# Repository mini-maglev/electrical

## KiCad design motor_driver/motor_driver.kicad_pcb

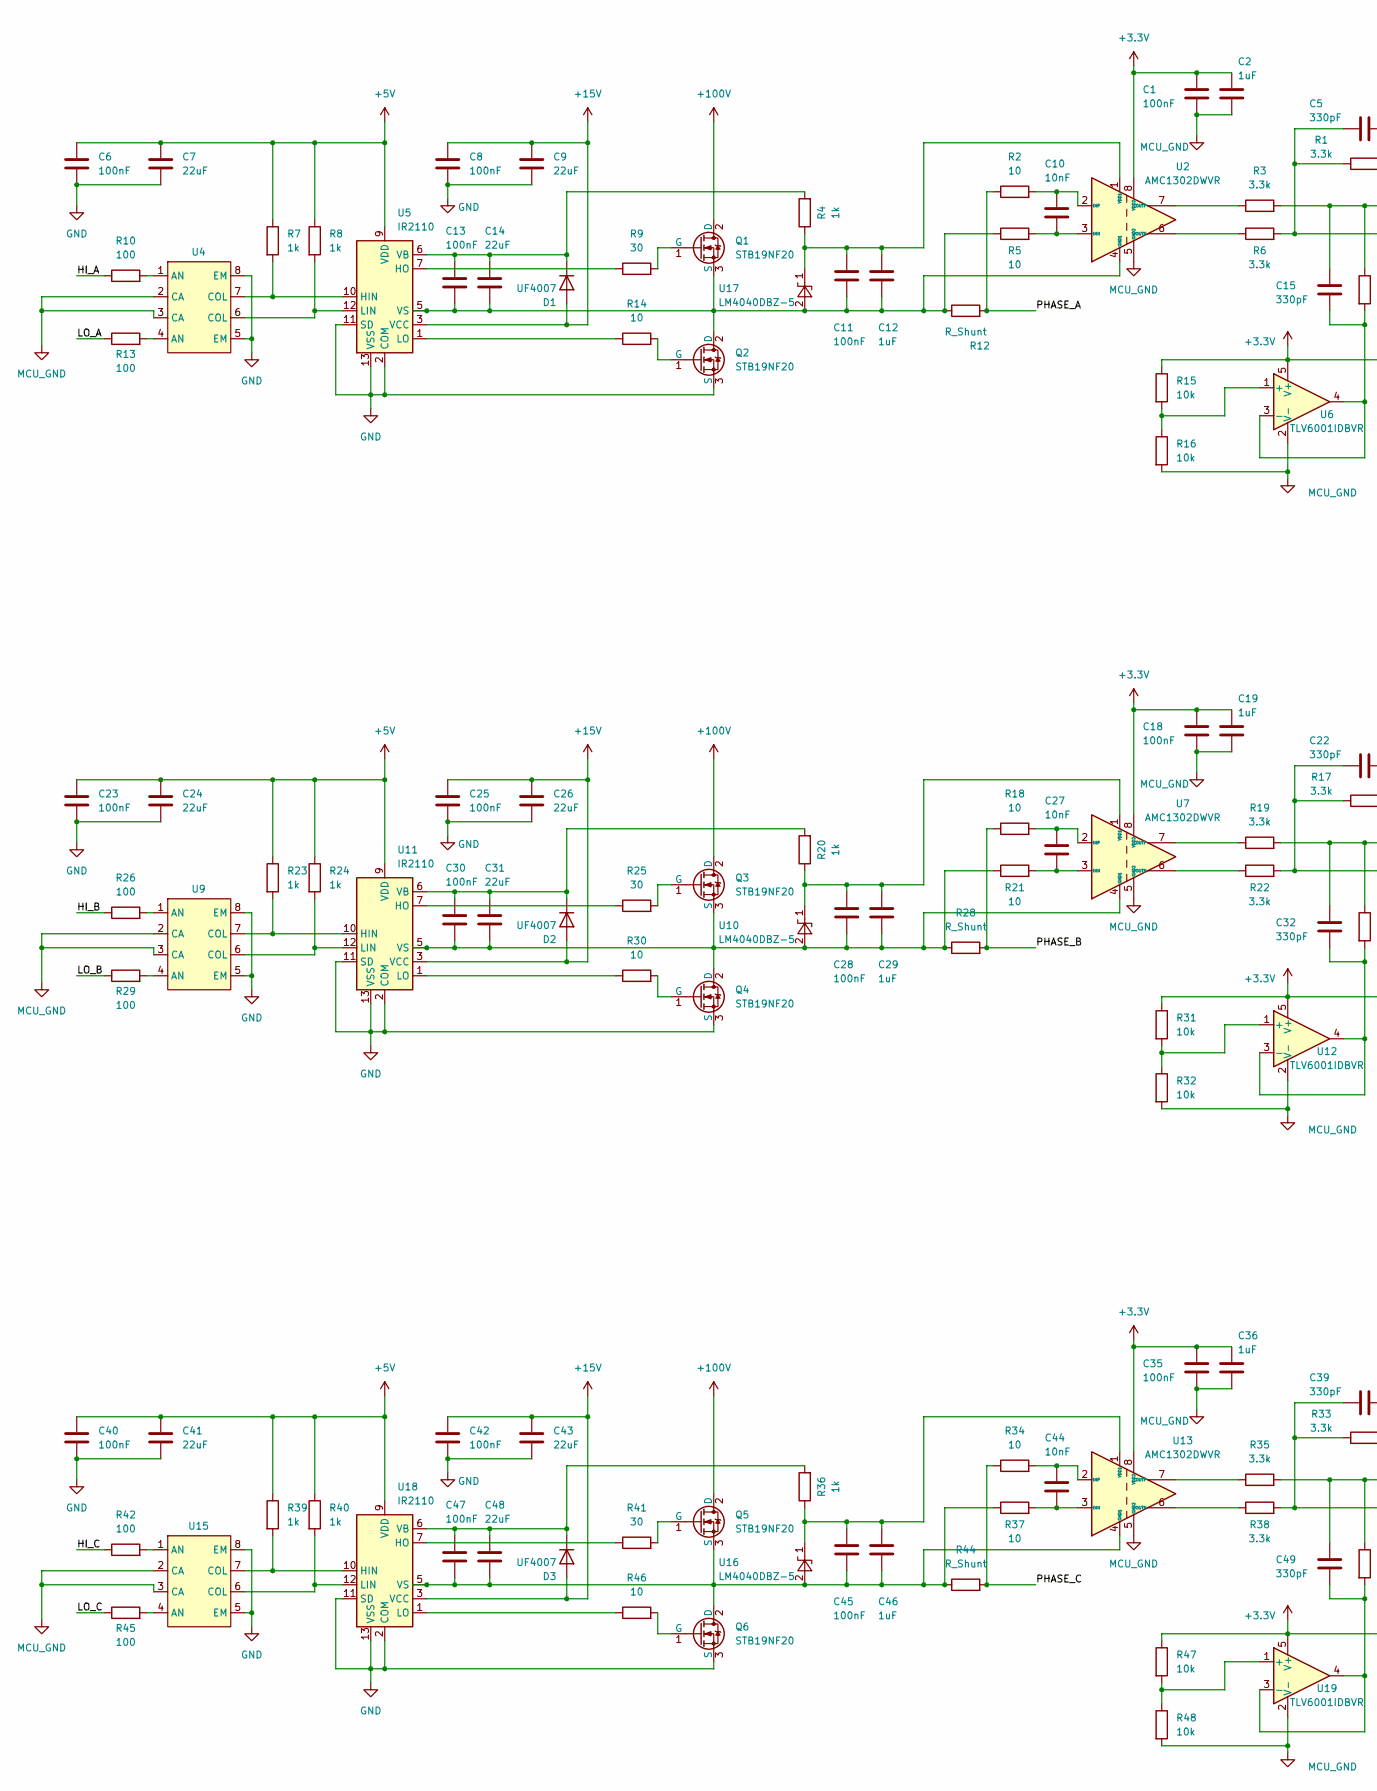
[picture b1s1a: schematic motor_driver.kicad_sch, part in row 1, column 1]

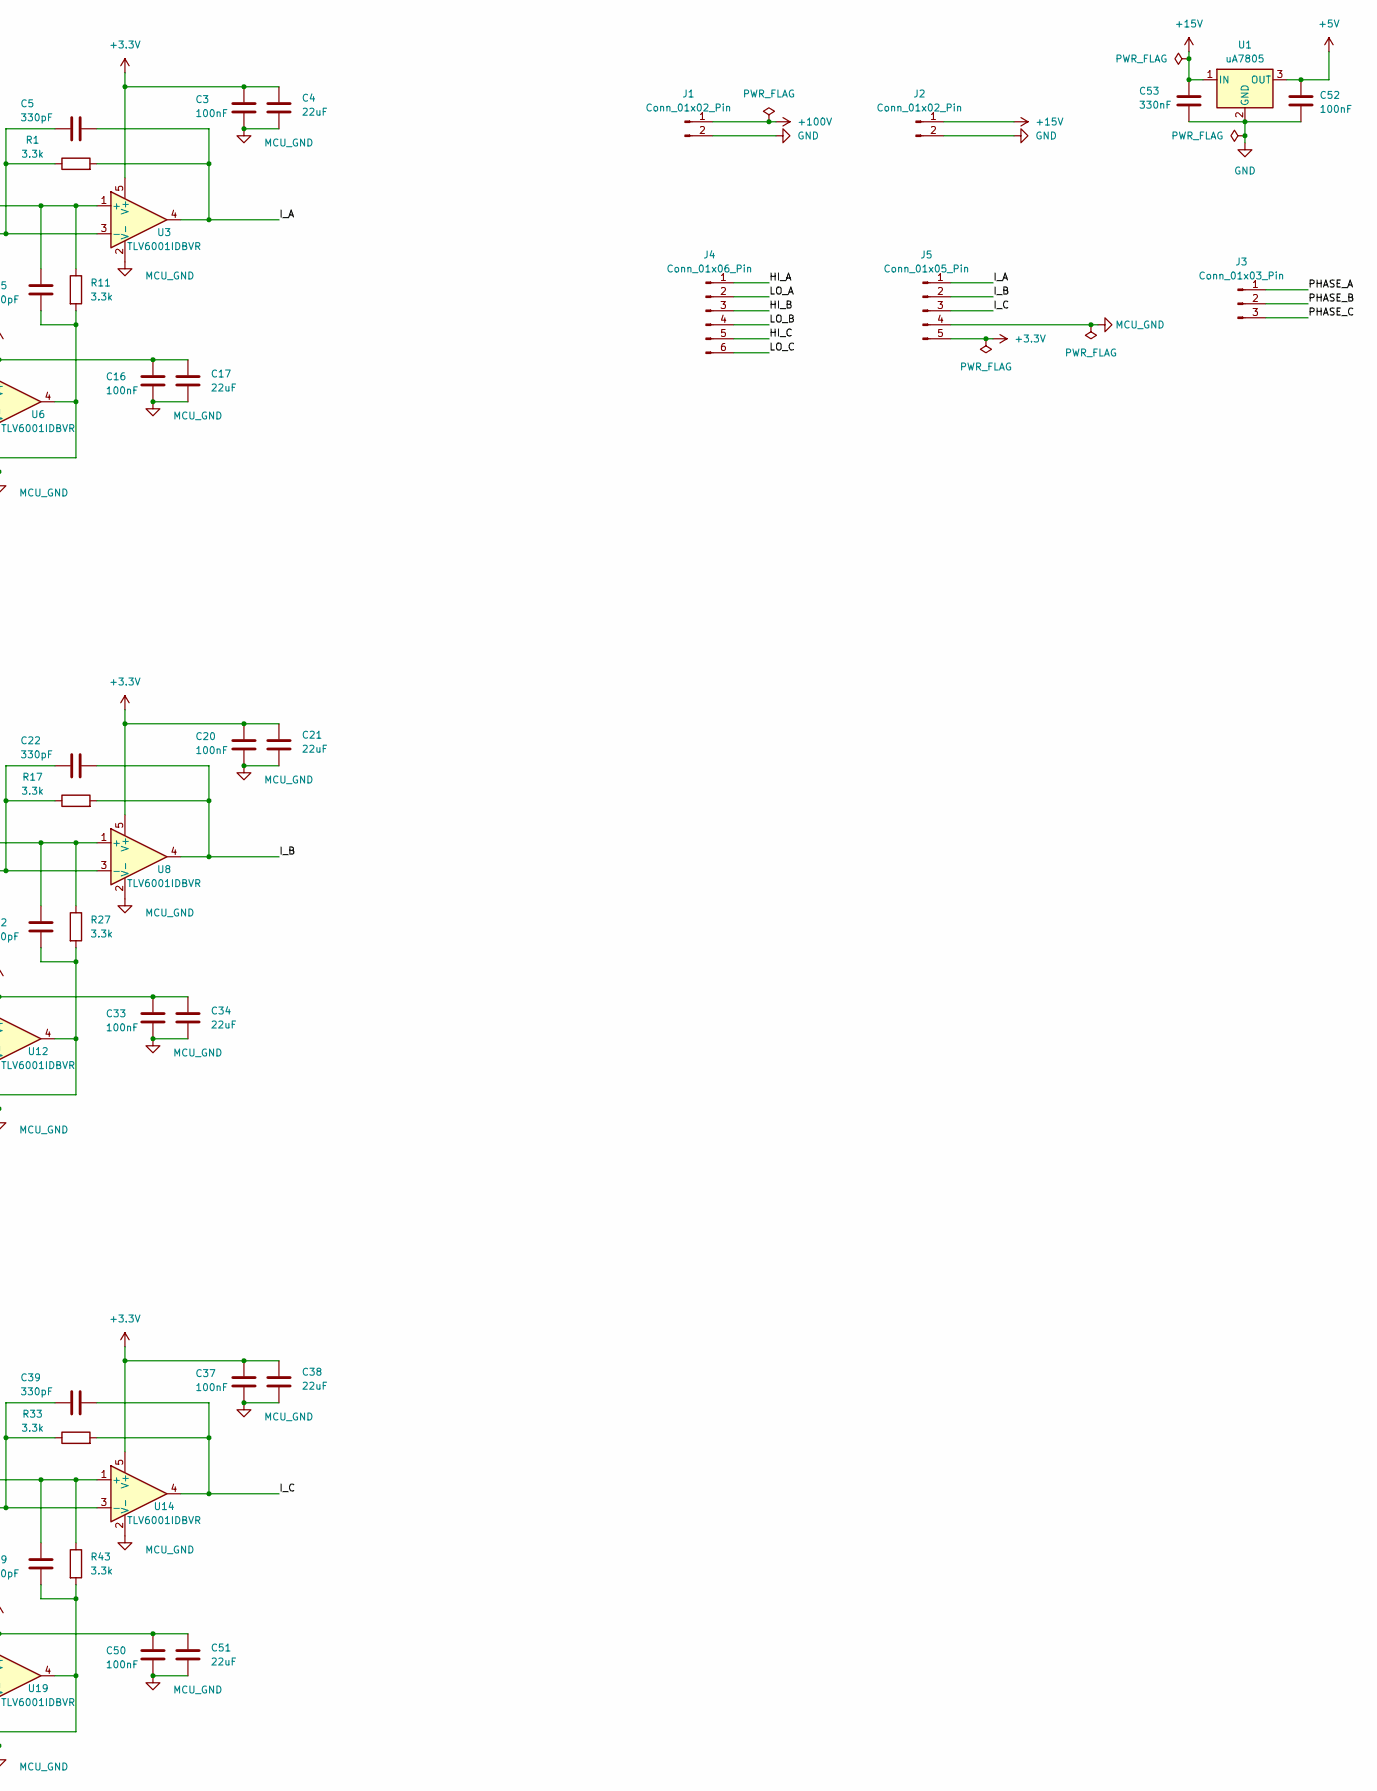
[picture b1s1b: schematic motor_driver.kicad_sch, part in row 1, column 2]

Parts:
C1, C3, C6, C8, C11, C13, C16, C18, C20, C23, C25, C28, C30, C33, C35, C37, C40, C42, C45, C47, C50, C52: 100nF; C_0603_1608Metric_Pad1.08x0.95mm_HandSolder
C2, C12, C19, C29, C36, C46: 1uF; C_0805_2012Metric_Pad1.18x1.45mm_HandSolder
C4, C7, C9, C14, C17, C21, C24, C26, C31, C34, C38, C41, C43, C48, C51: 22uF; C_0805_2012Metric_Pad1.18x1.45mm_HandSolder
C5, C15, C22, C32, C39, C49: 330pF; C_0402_1005Metric_Pad0.74x0.62mm_HandSolder
C10, C27, C44: 10nF; C_0402_1005Metric_Pad0.74x0.62mm_HandSolder
C53: 330nF; C_0805_2012Metric_Pad1.18x1.45mm_HandSolder
D1, D2, D3: UF4007; D_DO-41_SOD81_P10.16mm_Horizontal
J1: Conn_01x02_Pin; TerminalBlock_MetzConnect_Type067_RT01902HDWC_1x02_P10.00mm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
J2: Conn_01x02_Pin; TerminalBlock_MaiXu_MX126-5.0-02P_1x02_P5.00mm
J3: Conn_01x03_Pin; TerminalBlock_MetzConnect_Type067_RT01903HDWC_1x03_P10.00mm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
J4: Conn_01x06_Pin; PinHeader_1x06_P2.54mm_Vertical
J5: Conn_01x05_Pin; PinHeader_1x05_P2.54mm_Vertical
Q1, Q2, Q3, Q4, Q5, Q6: STB19NF20; TO-220-3_Vertical_Heat_Sink
R1, R3, R6, R11, R17, R19, R22, R27, R33, R35, R38, R43: 3.3k; R_0805_2012Metric_Pad1.20x1.40mm_HandSolder
R2, R5, R14, R18, R21, R30, R34, R37, R46: 10; R_1206_3216Metric_Pad1.30x1.75mm_HandSolder
R4, R20, R36: 1k; R_1206_3216Metric_Pad1.30x1.75mm_HandSolder
R7, R8, R23, R24, R39, R40: 1k; R_0805_2012Metric_Pad1.20x1.40mm_HandSolder
R9, R25, R41: 30; R_1206_3216Metric_Pad1.30x1.75mm_HandSolder
R10, R13, R26, R29, R42, R45: 100; R_0805_2012Metric_Pad1.20x1.40mm_HandSolder
R12, R44: R_Shunt; BVT-I-R003
R15, R16, R31, R32, R47, R48: 10k; R_0805_2012Metric_Pad1.20x1.40mm_HandSolder
R28: R_Shunt; BVT-I-R003_Reverse
U1: uA7805; TO-220-3_Vertical
U2, U7, U13: AMC1302DWVR; SOIC-8_7.5x5.85mm_P1.27mm
U3, U6, U8, U12, U14, U19: TLV6001IDBVR; SOT-23-5_HandSoldering
U4, U9, U15: MCT6
U5, U11, U18: IR2110; DIP-14_W7.62mm
U10, U16, U17: LM4040DBZ-5; SOT-23

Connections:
+3.3V: C1.1, C2.1, C3.1, C4.1, C16.1, C17.1, C18.1, C19.1, C20.1, C21.1, C33.1, C34.1, C35.1, C36.1, C37.1, C38.1, C50.1, C51.1, J5.5, R15.1, R31.1, R47.1, U2.8 (VDD2), U3.5 (V+), U6.5 (V+), U7.8 (VDD2), U8.5 (V+), U12.5 (V+), U13.8 (VDD2), U14.5 (V+), U19.5 (V+)
+5V: C6.1, C7.1, C23.1, C24.1, C40.1, C41.1, C52.1, R7.1, R8.1, R23.1, R24.1, R39.1, R40.1, U1.3 (OUT), U5.9 (VDD), U11.9 (VDD), U18.9 (VDD)
+15V: C8.1, C9.1, C25.1, C26.1, C42.1, C43.1, C53.1, D1.2 (A), D2.2 (A), D3.2 (A), J2.1, U1.1 (IN), U5.3 (VCC), U11.3 (VCC), U18.3 (VCC)
+100V: J1.1, Q1.2 (D), Q3.2 (D), Q5.2 (D)
/HI_A: J4.1, R10.1
/HI_B: J4.3, R26.1
/HI_C: J4.5, R42.1
/I_A: C5.1, J5.1, R1.2, U3.4
/I_B: C22.1, J5.2, R17.2, U8.4
/I_C: C39.1, J5.3, R33.2, U14.4
/LO_A: J4.2, R13.1
/LO_B: J4.4, R29.1
/LO_C: J4.6, R45.1
/PHASE_A: J3.1, R2.1, R12.2
/PHASE_B: J3.2, R18.1, R28.2
/PHASE_C: J3.3, R34.1, R44.2
GND: C6.2, C7.2, C8.2, C9.2, C23.2, C24.2, C25.2, C26.2, C40.2, C41.2, C42.2, C43.2, C52.2, C53.2, J1.2, J2.2, Q2.3 (S), Q4.3 (S), Q6.3 (S), U1.2 (GND), U4.5 (EM), U4.8 (EM), U5.2 (COM), U5.11 (SD), U5.13 (VSS), U9.5 (EM), U9.8 (EM), U11.2 (COM), U11.11 (SD), U11.13 (VSS), U15.5 (EM), U15.8 (EM), U18.2 (COM), U18.11 (SD), U18.13 (VSS)
MCU_GND: C1.2, C2.2, C3.2, C4.2, C16.2, C17.2, C18.2, C19.2, C20.2, C21.2, C33.2, C34.2, C35.2, C36.2, C37.2, C38.2, C50.2, C51.2, J5.4, R16.2, R32.2, R48.2, U2.5 (GND2), U3.2 (V-), U4.2 (CA), U4.3 (CA), U6.2 (V-), U7.5 (GND2), U8.2 (V-), U9.2 (CA), U9.3 (CA), U12.2 (V-), U13.5 (GND2), U14.2 (V-), U15.2 (CA), U15.3 (CA), U19.2 (V-)
unnamed: C13.1, C14.1, D1.1 (K), R4.2, U5.6 (VB)
unnamed: C30.1, C31.1, D2.1 (K), R20.2, U11.6 (VB)
unnamed: C47.1, C48.1, D3.1 (K), R36.2, U18.6 (VB)
unnamed: Q1.1 (G), R9.2
unnamed: C11.2, C12.2, C13.2, C14.2, Q1.3 (S), Q2.2 (D), R5.1, R12.1, U2.4 (GND1), U5.5 (VS), U17.2 (A)
unnamed: Q2.1 (G), R14.2
unnamed: Q3.1 (G), R25.2
unnamed: C28.2, C29.2, C30.2, C31.2, Q3.3 (S), Q4.2 (D), R21.1, R28.1, U7.4 (GND1), U10.2 (A), U11.5 (VS)
unnamed: Q4.1 (G), R30.2
unnamed: Q5.1 (G), R41.2
unnamed: C45.2, C46.2, C47.2, C48.2, Q5.3 (S), Q6.2 (D), R37.1, R44.1, U13.4 (GND1), U16.2 (A), U18.5 (VS)
unnamed: Q6.1 (G), R46.2
unnamed: R10.2, U4.1 (AN)
unnamed: R13.2, U4.4 (AN)
unnamed: R26.2, U9.1 (AN)
unnamed: R29.2, U9.4 (AN)
unnamed: R42.2, U15.1 (AN)
unnamed: R45.2, U15.4 (AN)
unnamed: C10.2, R5.2, U2.3 (INN)
unnamed: C10.1, R2.2, U2.2 (INP)
unnamed: R6.1, U2.6 (OUTN)
unnamed: R3.1, U2.7 (OUTP)
unnamed: C15.1, R3.2, R11.1, U3.1 (+)
unnamed: C5.2, R1.1, R6.2, U3.3 (-)
unnamed: R7.2, U4.7 (COL), U5.10 (HIN)
unnamed: R9.1, U5.7 (HO)
unnamed: R8.2, U4.6 (COL), U5.12 (LIN)
unnamed: R14.1, U5.1 (LO)
unnamed: R15.2, R16.1, U6.1 (+)
unnamed: C15.2, R11.2, U6.3 (-), U6.4
unnamed: C27.2, R21.2, U7.3 (INN)
unnamed: C27.1, R18.2, U7.2 (INP)
unnamed: R22.1, U7.6 (OUTN)
unnamed: R19.1, U7.7 (OUTP)
unnamed: C32.1, R19.2, R27.1, U8.1 (+)
unnamed: C22.2, R17.1, R22.2, U8.3 (-)
unnamed: C28.1, C29.1, R20.1, U7.1 (VDD1), U10.1 (K)
unnamed: R23.2, U9.7 (COL), U11.10 (HIN)
unnamed: R25.1, U11.7 (HO)
unnamed: R24.2, U9.6 (COL), U11.12 (LIN)
unnamed: R30.1, U11.1 (LO)
unnamed: R31.2, R32.1, U12.1 (+)
unnamed: C32.2, R27.2, U12.3 (-), U12.4
unnamed: C44.2, R37.2, U13.3 (INN)
unnamed: C44.1, R34.2, U13.2 (INP)
unnamed: R38.1, U13.6 (OUTN)
unnamed: R35.1, U13.7 (OUTP)
unnamed: C45.1, C46.1, R36.1, U13.1 (VDD1), U16.1 (K)
unnamed: C49.1, R35.2, R43.1, U14.1 (+)
unnamed: C39.2, R33.1, R38.2, U14.3 (-)
unnamed: C11.1, C12.1, R4.1, U2.1 (VDD1), U17.1 (K)
unnamed: R39.2, U15.7 (COL), U18.10 (HIN)
unnamed: R41.1, U18.7 (HO)
unnamed: R40.2, U15.6 (COL), U18.12 (LIN)
unnamed: R46.1, U18.1 (LO)
unnamed: R47.2, R48.1, U19.1 (+)
unnamed: C49.2, R43.2, U19.3 (-), U19.4

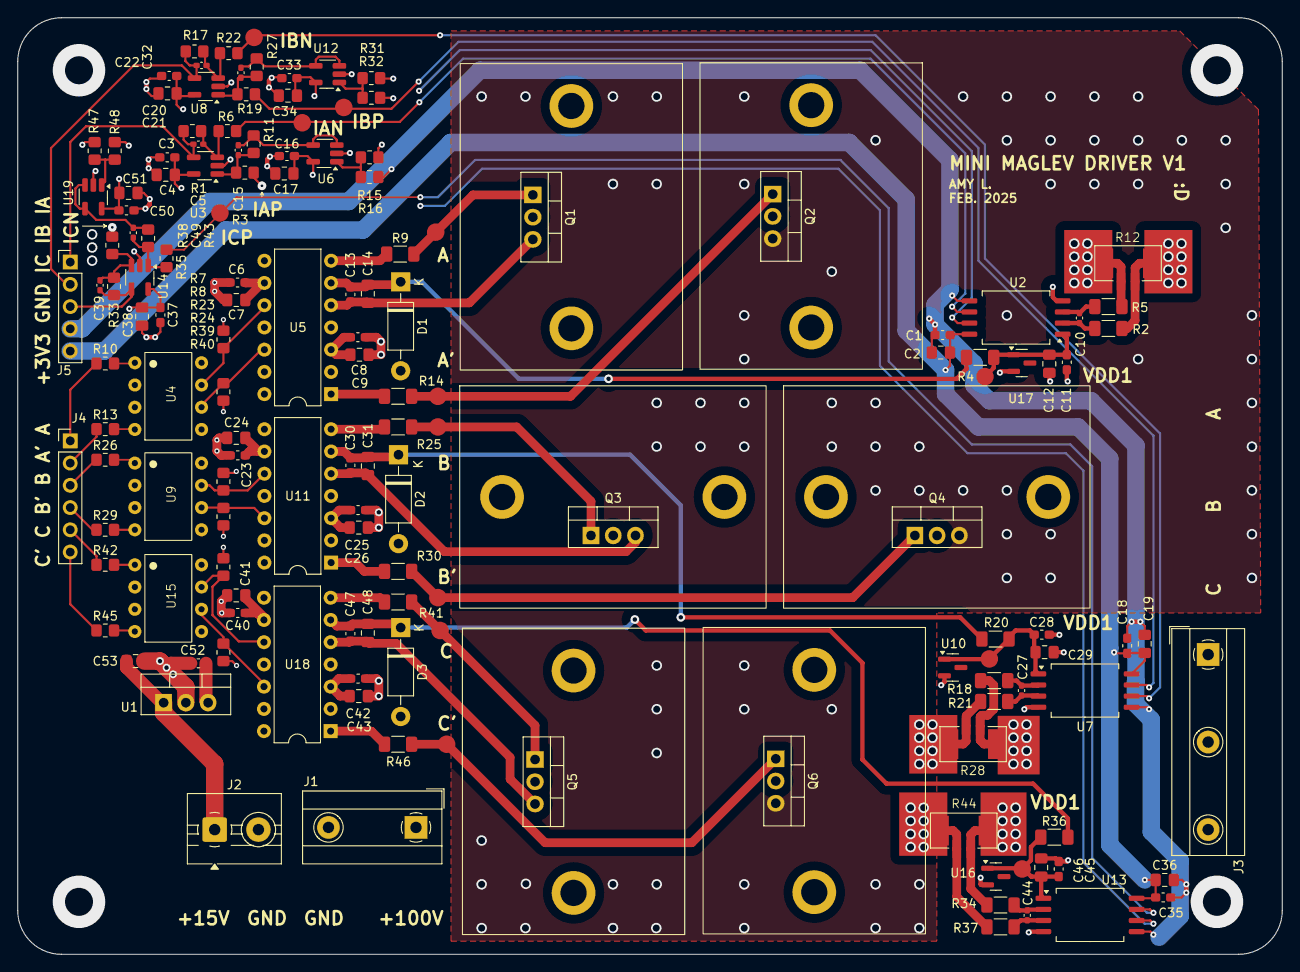
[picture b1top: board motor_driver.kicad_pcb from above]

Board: 4 copper layers, 144.5 x 107.0 mm, 134 parts (0 on the bottom side), 75 nets.

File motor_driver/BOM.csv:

Reference,Value,Footprint,Qty,DNP,,
"C1,C3,C6,C8,C11,C13,C16,C18,C20,C23,C25,C28,C30,C33,C35,C37,C40,C42,C45,C47,C50,C52",100nF,Capacitor_SMD:C_0603_1608Metric_Pad1.08x0.95mm_HandSolder,22,,,
"C2,C12,C19,C29,C36,C46",1uF,Capacitor_SMD:C_0805_2012Metric_Pad1.18x1.45mm_HandSolder,6,,,
"C4,C7,C9,C14,C17,C21,C24,C26,C31,C34,C38,C41,C43,C48,C51",22uF,Capacitor_SMD:C_0805_2012Metric_Pad1.18x1.45mm_HandSolder,15,,,
"C5,C15,C22,C32,C39,C49",330pF,Capacitor_SMD:C_0402_1005Metric_Pad0.74x0.62mm_HandSolder,6,,,
"C10,C27,C44",10nF,Capacitor_SMD:C_0402_1005Metric_Pad0.74x0.62mm_HandSolder,3,,,
C53,330nF,Capacitor_SMD:C_0805_2012Metric_Pad1.18x1.45mm_HandSolder,1,,,
"D1,D2,D3",UF4007,Diode_THT:D_DO-41_SOD81_P10.16mm_Horizontal,3,,,
"J1,J2",Conn_01x02_Pin,-- mixed values --,2,,,
J3,Conn_01x03_Pin,TerminalBlock_MetzConnect:TerminalBlock_MetzConnect_Type067_RT01903HDWC_1x03_P10.00mm_Horizontal,1,,,
J4,Conn_01x06_Pin,Connector_PinHeader_2.54mm:PinHeader_1x06_P2.54mm_Vertical,1,,,
J5,Conn_01x05_Pin,Connector_PinHeader_2.54mm:PinHeader_1x05_P2.54mm_Vertical,1,,,
"Q1,Q2,Q3,Q4,Q5,Q6",STB19NF20,Custom_footprints:TO-220-3_Vertical_Heat_Sink,6,,,
"R1,R3,R6,R11,R17,R19,R22,R27,R33,R35,R38,R43",3.3k,Resistor_SMD:R_0805_2012Metric_Pad1.20x1.40mm_HandSolder,12,,,
"R2,R5,R14,R18,R21,R30,R34,R37,R46",10,Resistor_SMD:R_1206_3216Metric_Pad1.30x1.75mm_HandSolder,9,,,
"R4,R7,R8,R20,R23,R24,R36,R39,R40",1k,-- mixed values --,9,,,
"R9,R25,R41",30,Resistor_SMD:R_1206_3216Metric_Pad1.30x1.75mm_HandSolder,3,,,
"R10,R13,R26,R29,R42,R45",100,Resistor_SMD:R_0805_2012Metric_Pad1.20x1.40mm_HandSolder,6,,,
"R12,R28,R44",R_Shunt,-- mixed values --,3,,,
"R15,R16,R31,R32,R47,R48",10k,Resistor_SMD:R_0805_2012Metric_Pad1.20x1.40mm_HandSolder,6,,,
U1,uA7805,Package_TO_SOT_THT:TO-220-3_Vertical,1,,,
"U2,U7,U13",AMC1302DWVR,Package_SO:SOIC-8_7.5x5.85mm_P1.27mm,3,,,
"U3,U6,U8,U12,U14,U19",TLV6001IDBVR,Package_TO_SOT_SMD:SOT-23-5_HandSoldering,6,,,
"U4,U9,U15",~,Custom_footprints:MCT6,3,,,
"U5,U11,U18",IR2110,Package_DIP:DIP-14_W7.62mm,3,,,
"U10,U16,U17",LM4040DBZ-5,Package_TO_SOT_SMD:SOT-23,3,,,

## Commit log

2025-01-11 upload LTspice file
2025-01-14 Current ripple simulation
2025-01-21 Current sensing diagram
2025-02-04 Test circuit schematics
2025-02-23 Driver schematic
2025-02-24 Change to isolation amp
2025-02-24 Add footprints
2025-02-28 Minor component changes
2025-03-02 Almost done
2025-03-02 Done
2025-03-02 Add 3d models
2025-03-02 Change test points from paste to mask layer as the should be
2025-03-02 Minor formatting change
2025-03-11 FEMM sim
2025-03-21 some scope traces
2025-03-28 More scope traces
2025-03-30 VFD test scope tracessS
